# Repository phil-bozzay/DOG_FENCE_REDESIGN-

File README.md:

## Members
Phillip Bozzay, Electrical Engineering Student (2027) phillipb23@vt.edu

## Mentor
Tyler Wells 

## Current Status
FINISHED

## Project Overview
Oscillator with center frequency of 10khz, and voltage amplitude from 1v-10v. Must run off of a +12volt supply and with a frequency range from 9.5k to 10.5k. 
Drive a 100ohm load with lightning protection.

## Educational Value Added
Electronic circuit design (oscillator, amplifier, fault protection) and custom pcb design. 

## Tasks
- add ground plane without ruining the converter 
- fix L1, L2 footprint
- switch potentiometer footprints
- verify frequency response 
- add lightning protection 

## Parts Order list 
- MBR0520L diode           (x1)
- LT1931A DC-DC converter  (x1)
- CR43NP-100MC inductors   (x2) 
 
## Design Decisions
(https://docs.google.com/drawings/d/1fAMgajhe5bFiq8WKqeaZG5vLBAoIA1WhgEOLgjycgV0/edit?pli=1)

## Design Misc

<!-- Your Text Here. You may work with your mentor on this later when they are assigned -->

## Steps for Documenting Your Design Process

<!-- Your Text Here. You may work with your mentor on this later when they are assigned -->

## BOM + Component Cost

<!-- Your Text Here. You may work with your mentor on this later when they are assigned -->

## Timeline

<!-- Your Text Here. You may work with your mentor on this later when they are assigned -->

## Useful Links

<!-- Your Text Here. You may work with your mentor on this later when they are assigned -->

## Log

<!-- Your Text Here. You may work with your mentor on this later when they are assigned -->

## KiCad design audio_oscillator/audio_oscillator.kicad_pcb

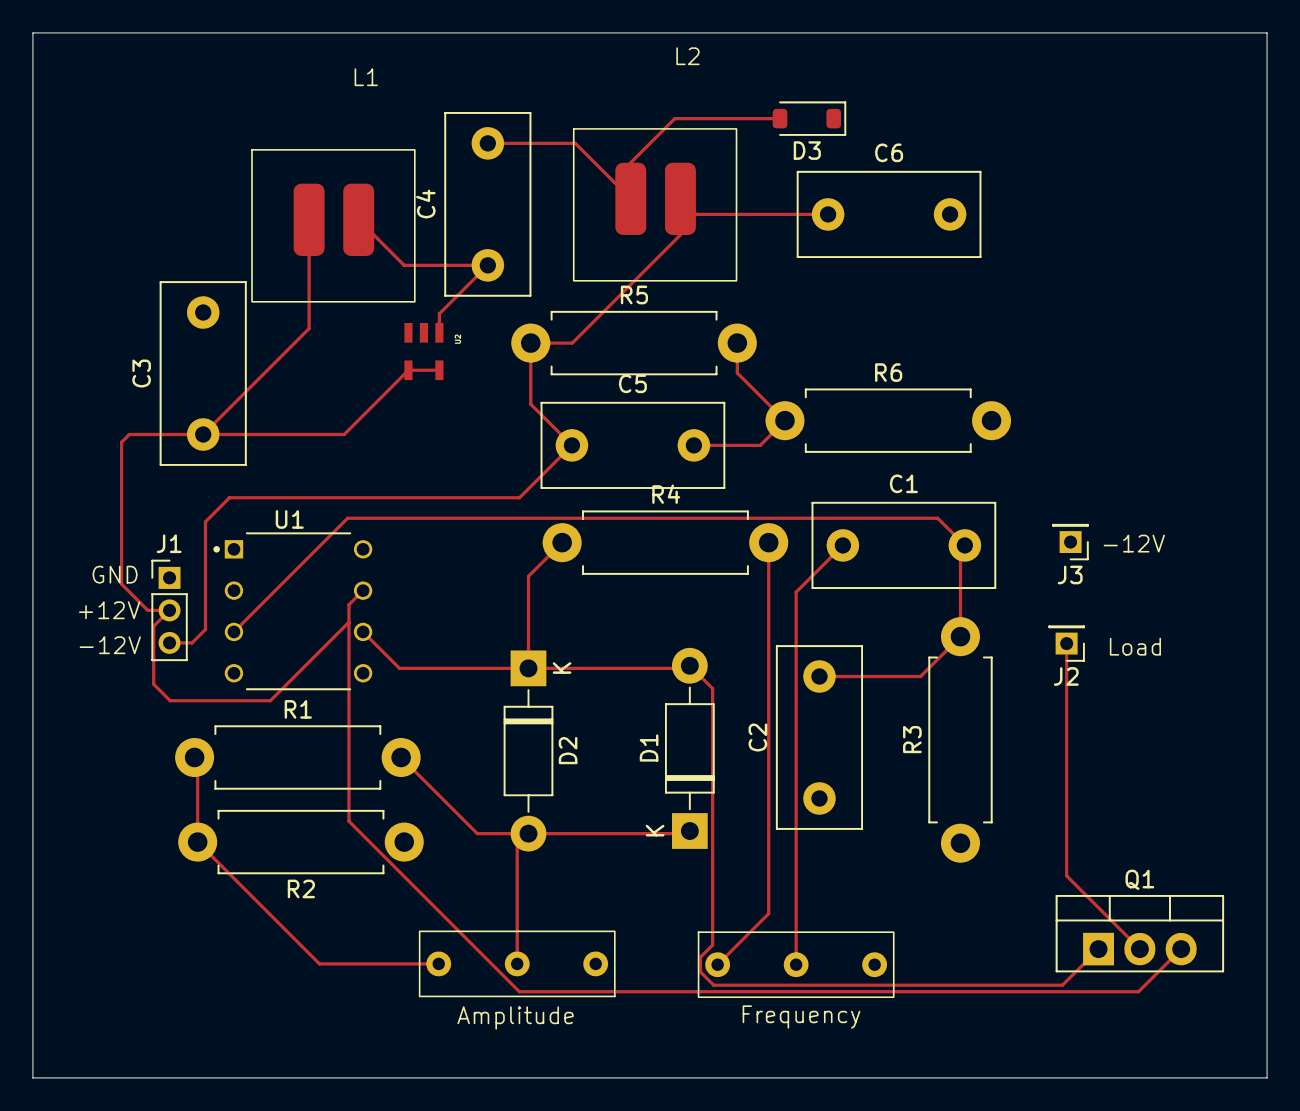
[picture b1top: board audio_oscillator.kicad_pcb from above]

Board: 2 copper layers, 75.9 x 64.2 mm, 25 parts (0 on the bottom side), 13 nets.

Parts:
C1, C2: 10n; C_Disc_D11.0mm_W5.0mm_P7.50mm
C3: 4.7u; C_Disc_D11.0mm_W5.0mm_P7.50mm
C4: 1u; C_Disc_D11.0mm_W5.0mm_P7.50mm
C5: 68p; C_Disc_D11.0mm_W5.0mm_P7.50mm
C6: 10u; C_Disc_D11.0mm_W5.0mm_P7.50mm
D1, D2: 1N4001; D_DO-41_SOD81_P10.16mm_Horizontal
D3: MBR0520; D_SOD-123
J1: Conn_01x03_Socket; PinHeader_1x03_P2.00mm_Vertical
J2, J3: Conn_01x01_Socket; PinHeader_1x01_P2.00mm_Vertical
L1, L2: 10u; Inductor_CR43NP
Q1: TIP41; TO-220-3_Vertical
R1: 5.6k; R_Axial_DIN0411_L9.9mm_D3.6mm_P12.70mm_Horizontal
R2: 2.7k; R_Axial_DIN0411_L9.9mm_D3.6mm_P12.70mm_Horizontal
R3, R4: 1.6k; R_Axial_DIN0411_L9.9mm_D3.6mm_P12.70mm_Horizontal
R5: 80.5k; R_Axial_DIN0411_L9.9mm_D3.6mm_P12.70mm_Horizontal
R6: 10k; R_Axial_DIN0411_L9.9mm_D3.6mm_P12.70mm_Horizontal
RV1: 100k; phil_pot
RV2: 1k; phil_pot
U1: LF356N; DIP794W45P254L959H508Q8
U2: LT1931AES5TRMPBF; SOT-5_S

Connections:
GND: C2.1, C3.2, C6.2, D3.1 (K), J1.1, J3.1, R2.1, R3.1, R6.2, RV1.3, U2.2 (GND)
unnamed: C1.1, RV2.2
unnamed: C1.2, C2.2, R3.2, U1.3 (IN)
unnamed: D1.2 (A), D2.1 (K), Q1.1 (B), R4.1, U1.6 (OUT)
unnamed: D1.1 (K), D2.2 (A), R1.2, RV1.2
unnamed: C4.2, D3.2 (A), L2.1
unnamed: C3.1, J1.2, L1.1, Q1.3 (E), U1.4 (V-), U1.7 (V+), U2.4 (*SHDN), U2.5 (VIN)
unnamed: C5.1, C6.1, J1.3, L2.2, R5.1
unnamed: J2.1, Q1.2 (C)
unnamed: R1.1, R2.2, RV1.1, U1.2 (IN)
unnamed: R4.2, RV2.3
unnamed: C5.2, R5.2, R6.1, U2.3 (NFB)
unnamed: C4.1, L1.2, U2.1 (SW)

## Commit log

2025-04-14 Added ki-cad files

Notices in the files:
parts and their libraries:
COPYRIGHT: Copyright C 2016 Accelerated Designs. All rights reserved
